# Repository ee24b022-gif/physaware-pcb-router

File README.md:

# physaware-pcb-router

Physics-aware PCB routing research code for switching power stages (buck converter hot loops).

**Status:** early development. **Keep this repository private** until a patent filing decision has been made.

## Layout

See `docs/architecture.md` for the package map, dependency rules, IR design decisions, and graph schema.

```python
from pcbroute.kicad_io import read_kicad
from pcbroute.ir import ir_from_kicad
from pcbroute.graph import build_graph

design = ir_from_kicad(read_kicad("board.kicad_pcb").model)    # Stage A: canonical IR
assert not [i for i in design.validate() if i.level == "error"]
graph = build_graph(design)                                    # Stage C: heterogeneous graph (numpy)
data = graph.to_pyg()                                          # torch_geometric HeteroData (needs the ml extra)
```

## Reading KiCad files

```bash
python -m pcbroute.kicad_io path/to/file.kicad_pcb      # or .kicad_sch, .net, .kicad_mod, .kicad_pro, .dsn ...
python -m pcbroute.kicad_io path/to/project_dir          # board + all schematic sheets + net classes
python -m pcbroute.kicad_io file.kicad_pcb --json        # full parsed model
python -m pcbroute.kicad_io file.kicad_sch --tree 3      # raw S-expression tree
```

```python
from pcbroute.kicad_io import read_kicad, read_project
board = read_kicad("buck.kicad_pcb").model     # pcbroute.board.Board
proj = read_project("my_project_dir")           # .settings, .board, .schematics
```

For schematic connectivity, export a netlist with `kicad-cli sch export netlist` and read the `.net` file.

## Roadmap

1. **Gate 0**: headroom test. Does a routing gap exist between a prioritized heuristic and an expert layout?
2. **Gate 1**: surrogate estimator (accuracy and ranking against FastHenry)
3. **Gate 2**: router PoC in simulation vs Freerouting and ablations
4. **Gate 3**: fabricated boards and measurements

## Dev setup

```bash
python -m venv .venv && source .venv/bin/activate
pip install -e ".[dev]"
pytest
```

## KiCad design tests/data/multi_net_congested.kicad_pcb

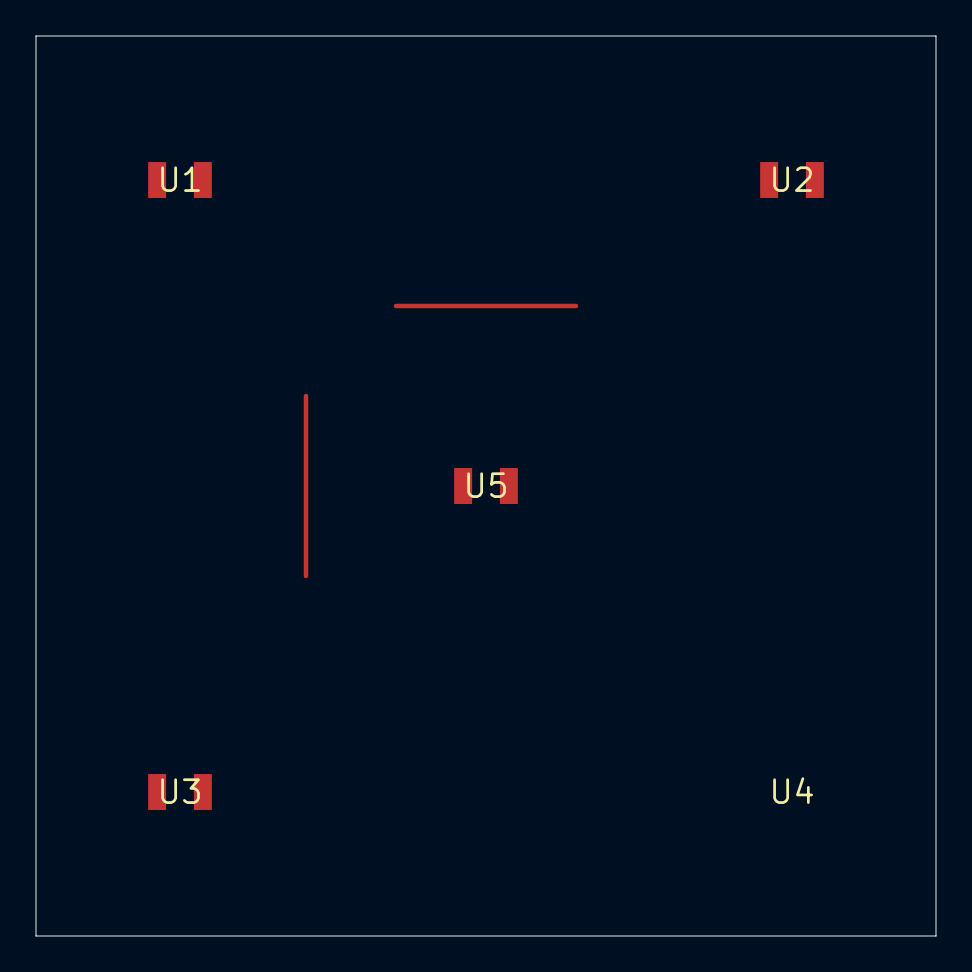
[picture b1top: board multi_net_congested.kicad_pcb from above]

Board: 2 copper layers, 50.0 x 50.0 mm, 5 parts (1 on the bottom side), 4 nets.

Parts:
U1, U2, U3, U4, U5: TEST; Footprint_2pin

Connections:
GND: U4.2, U5.1, U5.2
NET_1: U1.1, U2.1
NET_2: U1.2, U3.1
NET_3: U2.2, U4.1

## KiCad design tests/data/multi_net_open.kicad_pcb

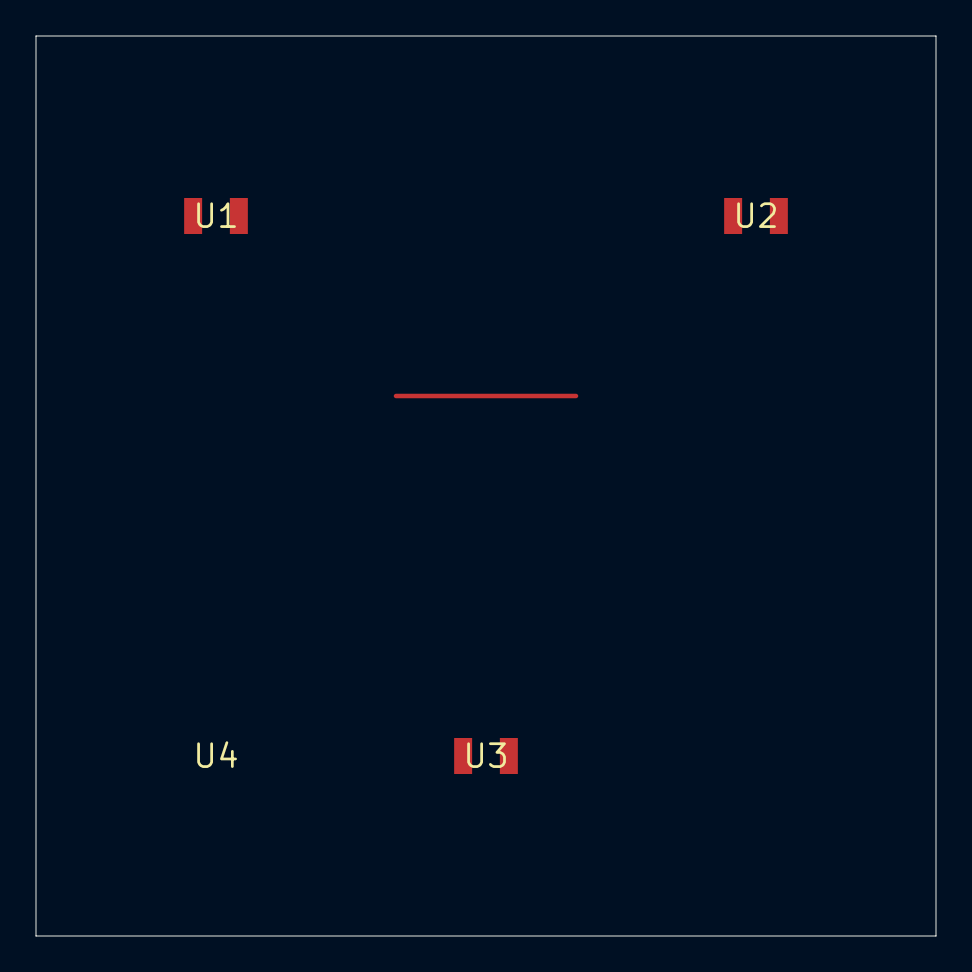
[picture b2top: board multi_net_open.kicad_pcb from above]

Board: 2 copper layers, 50.0 x 50.0 mm, 4 parts (1 on the bottom side), 3 nets.

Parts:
U1, U2, U3, U4: TEST; Footprint_2pin

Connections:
GND: U3.2, U4.1
NET_1: U1.1, U2.1, U4.2
NET_2: U1.2, U3.1

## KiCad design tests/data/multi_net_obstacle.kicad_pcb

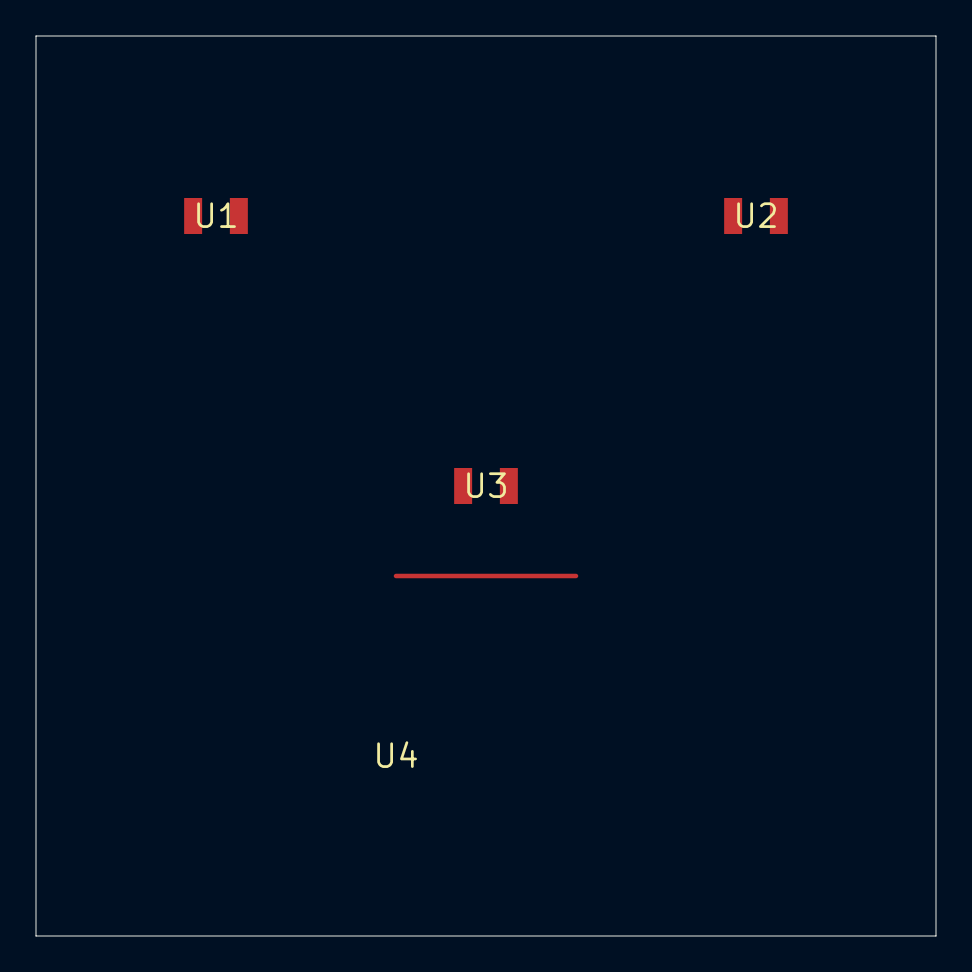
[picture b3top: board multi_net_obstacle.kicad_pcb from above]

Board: 2 copper layers, 50.0 x 50.0 mm, 4 parts (1 on the bottom side), 3 nets.

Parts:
U1, U2, U3, U4: TEST; Footprint_2pin

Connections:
GND: U4.1, U4.2
NET_A: U1.1, U2.1
NET_B: U1.2, U2.2, U3.1
